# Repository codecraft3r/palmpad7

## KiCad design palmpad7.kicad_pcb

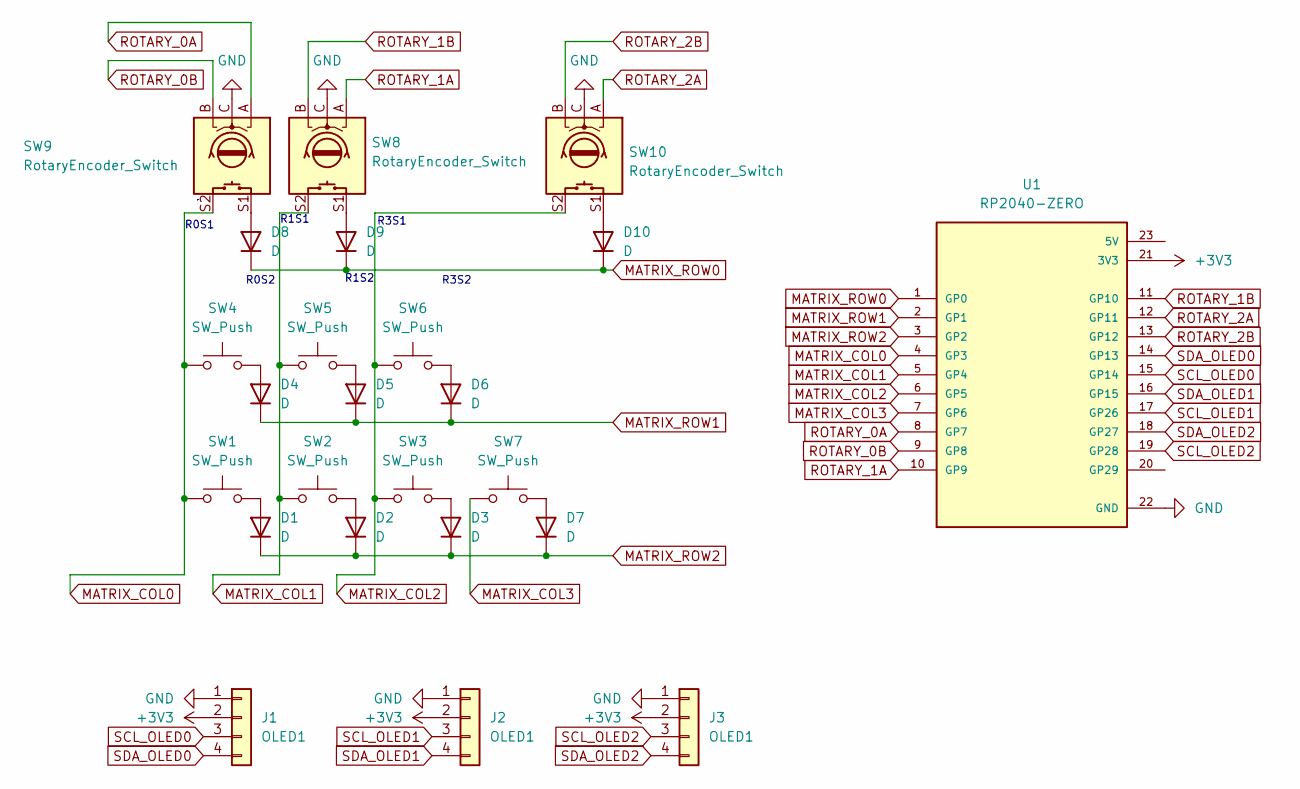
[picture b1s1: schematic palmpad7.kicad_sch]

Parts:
D1, D2, D3, D4, D5, D6, D7, D8, D9, D10: D; D_DO-35_SOD27_P7.62mm_Horizontal
J1, J2, J3: OLED1; PinSocket_1x04_P2.54mm_Vertical
SW1, SW2, SW3, SW4, SW5, SW6, SW7: SW_Push; SW_Cherry_MX_1.00u_PCB
SW8, SW9, SW10: RotaryEncoder_Switch; RotaryEncoder_Alps_EC11E-Switch_Vertical_H20mm
U1: RP2040-ZERO; MODULE_RP2040-ZERO; PARTREV NA

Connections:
+3V3: J1.2, J2.2, J3.2, U1.21 (3V3)
GND: J1.1, J2.1, J3.1, SW8.C, SW9.C, SW10.C, U1.22 (GND)
MATRIX_COL0: SW1.1, SW4.1, SW9.S2, U1.4 (GP3)
MATRIX_COL1: SW2.1, SW5.1, SW8.S2, U1.5 (GP4)
MATRIX_COL2: SW3.1, SW6.1, SW10.S2, U1.6 (GP5)
MATRIX_COL3: SW7.1, U1.7 (GP6)
MATRIX_ROW0: D8.1 (K), D9.1 (K), D10.1 (K), U1.1 (GP0)
MATRIX_ROW1: D4.1 (K), D5.1 (K), D6.1 (K), U1.2 (GP1)
MATRIX_ROW2: D1.1 (K), D2.1 (K), D3.1 (K), D7.1 (K), U1.3 (GP2)
unnamed: D1.2 (A), SW1.2
unnamed: D2.2 (A), SW2.2
unnamed: D3.2 (A), SW3.2
unnamed: D4.2 (A), SW4.2
unnamed: D5.2 (A), SW5.2
unnamed: D6.2 (A), SW6.2
unnamed: D7.2 (A), SW7.2
unnamed: D8.2 (A), SW9.S1
unnamed: D9.2 (A), SW8.S1
unnamed: D10.2 (A), SW10.S1
ROTARY_0A: SW9.A, U1.8 (GP7)
ROTARY_0B: SW9.B, U1.9 (GP8)
ROTARY_1A: SW8.A, U1.10 (GP9)
ROTARY_1B: SW8.B, U1.11 (GP10)
ROTARY_2A: SW10.A, U1.12 (GP11)
ROTARY_2B: SW10.B, U1.13 (GP12)
SCL_OLED0: J1.3, U1.15 (GP14)
SCL_OLED1: J2.3, U1.17 (GP26)
SCL_OLED2: J3.3, U1.19 (GP28)
SDA_OLED0: J1.4, U1.14 (GP13)
SDA_OLED1: J2.4, U1.16 (GP15)
SDA_OLED2: J3.4, U1.18 (GP27)

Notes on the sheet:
R1S2
R0S2
R3S1
R0S1
R1S1
R3S2

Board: 2 copper layers, 24 parts (7 on the bottom side), 31 nets, no tracks yet.

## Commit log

2025-08-24 init
2025-08-24 add libraries
2025-09-14 kicad files
2025-09-14 Use labels and add OLEDs on schematic
2025-09-14 Add MacOS specific files to .gitignore
2025-09-14 Fix OLED pins
2025-09-14 start pcb
